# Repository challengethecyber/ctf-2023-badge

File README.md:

# ctf-2023-badge
Badge related files for CTC 2023 CTF

## Info

- Custom PCB with RP2040 based on [rp-micro](https://github.com/siderakb/rp-micro) project.
- View [IBOM](https://challengethecyber.github.io/ctf-2023-assets/ducky/ibom.html)

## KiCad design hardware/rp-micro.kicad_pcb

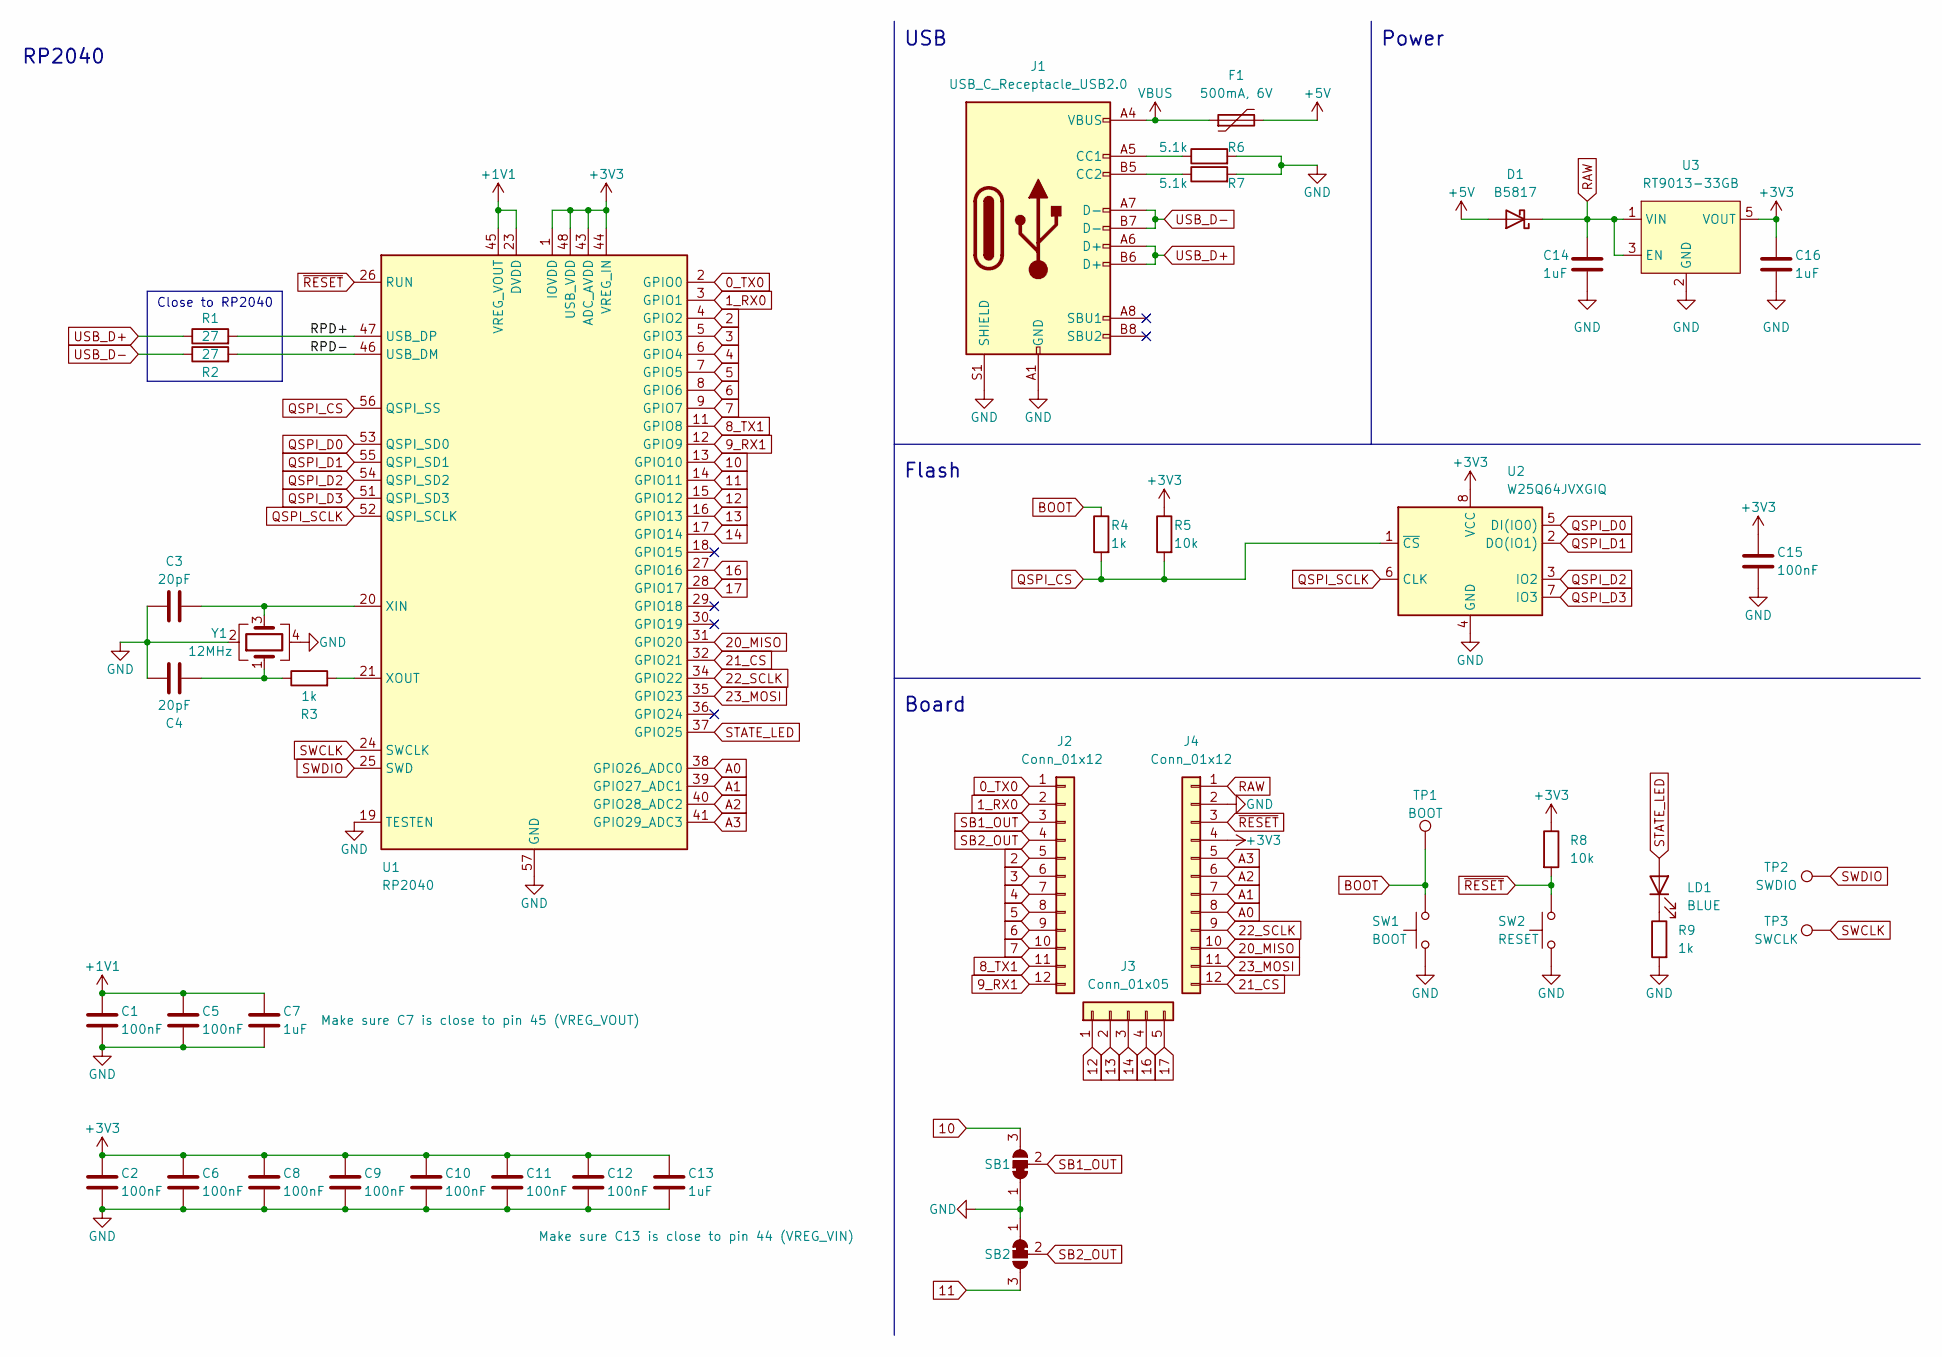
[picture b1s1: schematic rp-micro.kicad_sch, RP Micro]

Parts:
C1, C2, C5, C6, C8, C9, C10, C11, C12, C15: 100nF; C_0402_1005Metric; MFR. Part # CL05B104KB54PNC; JLCPCB Part # C307331
C3, C4: 20pF; C_0402_1005Metric; MFR. Part # 0402CG200J500NT; JLCPCB Part # C1554
C7, C13, C14, C16: 1uF; C_0402_1005Metric; MFR. Part # CL05A105KA5NQNC; JLCPCB Part # C52923
D1: B5817; D_SOD-323_HandSoldering; MFR. Part # B5817WS; JLCPCB Part # C123899
F1: 500mA, 6V; Fuse_0805_2012Metric; MFR. Part # SMD0805B050TF; JLCPCB Part # C269104
J1: USB_C_Receptacle_USB2.0; USB Type-C Mid-Mount Receptacle 16P; MFR. Part # 918-418K2024S40000; JLCPCB Part # C168688
J2, J4: Conn_01x12; PinHeader_1x12_P2.54mm_Vertical
J3: Conn_01x05; PinHeader_1x05_P2.54mm_Vertical
LD1: BLUE; LED_0603_1608Metric; MFR. Part # 19-217/BHC-ZL1M2RY/3T; JLCPCB Part # C72041
R1, R2: 27; R_0402_1005Metric; MFR. Part # 0402WGF270JTCE; JLCPCB Part # C25100
R3, R4, R9: 1k; R_0402_1005Metric; MFR. Part # 0402WGF1001TCE; JLCPCB Part # C11702
R5, R8: 10k; R_0402_1005Metric; MFR. Part # 0402WGF1002TCE; JLCPCB Part # C25744
R6, R7: 5.1k; R_0402_1005Metric; MFR. Part # 0402WGF5101TCE; JLCPCB Part # C25905
SB1, SB2: SolderJumper_3_Bridged12; SolderJumper-3_P1.3mm_Bridged12_Pad1.0x1.5mm
SW1: BOOT; SW_SPST_B3U-1000P; MFR. Part # B3U-1000P; JLCPCB Part # C231329
SW2: RESET; SW_SPST_B3U-1000P; MFR. Part # B3U-1000P; JLCPCB Part # C231329
TP1: BOOT; TestPoint_Pad_D2.0mm
TP2: SWDIO; TestPoint_Pad_D2.0mm
TP3: SWCLK; TestPoint_Pad_D2.0mm
U1: RP2040; QFN-56-1EP_7x7mm_P0.4mm_EP3.2x3.2mm; MFR. Part # RP2040; JLCPCB Part # C2040
U2: W25Q64JVXGIQ; XSON-8 (4x4mm); MFR. Part # W25Q64JVXGIQ; JLCPCB Part # C2940195
U3: RT9013-33GB; SOT-23-5; MFR. Part # RT9013-33GB; JLCPCB Part # C47773
Y1: 12MHz; Crystal_SMD_3225-4Pin_3.2x2.5mm; MFR. Part # X322512MSB4SI; JLCPCB Part # C9002

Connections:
0_TX0: J2.1, U1.2 (GPIO0)
1_RX0: J2.2, U1.3 (GPIO1)
2: J2.5, U1.4 (GPIO2)
3: J2.6, U1.5 (GPIO3)
4: J2.7, U1.6 (GPIO4)
5: J2.8, U1.7 (GPIO5)
6: J2.9, U1.8 (GPIO6)
7: J2.10, U1.9 (GPIO7)
8_TX1: J2.11, U1.11 (GPIO8)
9_RX1: J2.12, U1.12 (GPIO9)
10: SB1.3 (B), U1.13 (GPIO10)
11: SB2.3 (B), U1.14 (GPIO11)
12: J3.1, U1.15 (GPIO12)
13: J3.2, U1.16 (GPIO13)
14: J3.3, U1.17 (GPIO14)
16: J3.4, U1.27 (GPIO16)
17: J3.5, U1.28 (GPIO17)
20_MISO: J4.10, U1.31 (GPIO20)
21_CS: J4.12, U1.32 (GPIO21)
22_SCLK: J4.9, U1.34 (GPIO22)
23_MOSI: J4.11, U1.35 (GPIO23)
+1V1: C1.1, C5.1, C7.1, U1.23 (DVDD), U1.45 (VREG_VOUT), U1.50 (DVDD)
+3V3: C2.1, C6.1, C8.1, C9.1, C10.1, C11.1, C12.1, C13.1, C15.1, C16.1, J4.4, R5.1, R8.1, U1.1 (IOVDD), U1.10 (IOVDD), U1.22 (IOVDD), U1.33 (IOVDD), U1.42 (IOVDD), U1.43 (ADC_AVDD), U1.44 (VREG_IN), U1.48 (USB_VDD), U1.49 (IOVDD), U2.8 (VCC), U3.5 (VOUT)
+5V: D1.2 (A), F1.2
/RPD+: R1.2, U1.47 (USB_DP)
/RPD-: R2.2, U1.46 (USB_DM)
A0: J4.8, U1.38 (GPIO26_ADC0)
A1: J4.7, U1.39 (GPIO27_ADC1)
A2: J4.6, U1.40 (GPIO28_ADC2)
A3: J4.5, U1.41 (GPIO29_ADC3)
BOOT: R4.1, SW1.2, TP1.1
GND: C1.2, C2.2, C3.1, C4.1, C5.2, C6.2, C7.2, C8.2, C9.2, C10.2, C11.2, C12.2, C13.2, C14.2, C15.2, C16.2, J1.A1 (GND), J1.A12 (GND), J1.B1 (GND), J1.B12 (GND), J1.S1 (SHIELD), J4.2, R6.2, R7.2, R9.2, SB1.1 (A), SB2.1 (A), SW1.1, SW2.1, U1.19 (TESTEN), U1.57 (GND), U2.4 (GND), U3.2 (GND), Y1.2, Y1.4
unnamed: C3.2, U1.20 (XIN), Y1.3
unnamed: C4.2, R3.1, Y1.1
unnamed: J1.A5 (CC1), R6.1
unnamed: J1.B5 (CC2), R7.1
unnamed: LD1.1 (K), R9.1
unnamed: R3.2, U1.21 (XOUT)
QSPI_CS: R4.2, R5.2, U1.56 (QSPI_SS), U2.1 (~CS)
QSPI_D0: U1.53 (QSPI_SD0), U2.5 (DI(IO0))
QSPI_D1: U1.55 (QSPI_SD1), U2.2 (DO(IO1))
QSPI_D2: U1.54 (QSPI_SD2), U2.3 (IO2)
QSPI_D3: U1.51 (QSPI_SD3), U2.7 (IO3)
QSPI_SCLK: U1.52 (QSPI_SCLK), U2.6 (CLK)
RAW: C14.1, D1.1 (K), J4.1, U3.1 (VIN), U3.3 (EN)
SB1_OUT: J2.3, SB1.2 (C)
SB2_OUT: J2.4, SB2.2 (C)
STATE_LED: LD1.2 (A), U1.37 (GPIO25)
SWCLK: TP3.1, U1.24 (SWCLK)
SWDIO: TP2.1, U1.25 (SWD)
USB_D+: J1.A6 (D+), J1.B6 (D+), R1.1
USB_D-: J1.A7 (D-), J1.B7 (D-), R2.1
VBUS: F1.1, J1.A4 (VBUS), J1.A9 (VBUS), J1.B4 (VBUS), J1.B9 (VBUS)
~RESET: J4.3, R8.2, SW2.2, U1.26 (RUN)

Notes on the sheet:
Flash
Close to RP2040
Power
RP2040
USB
Board

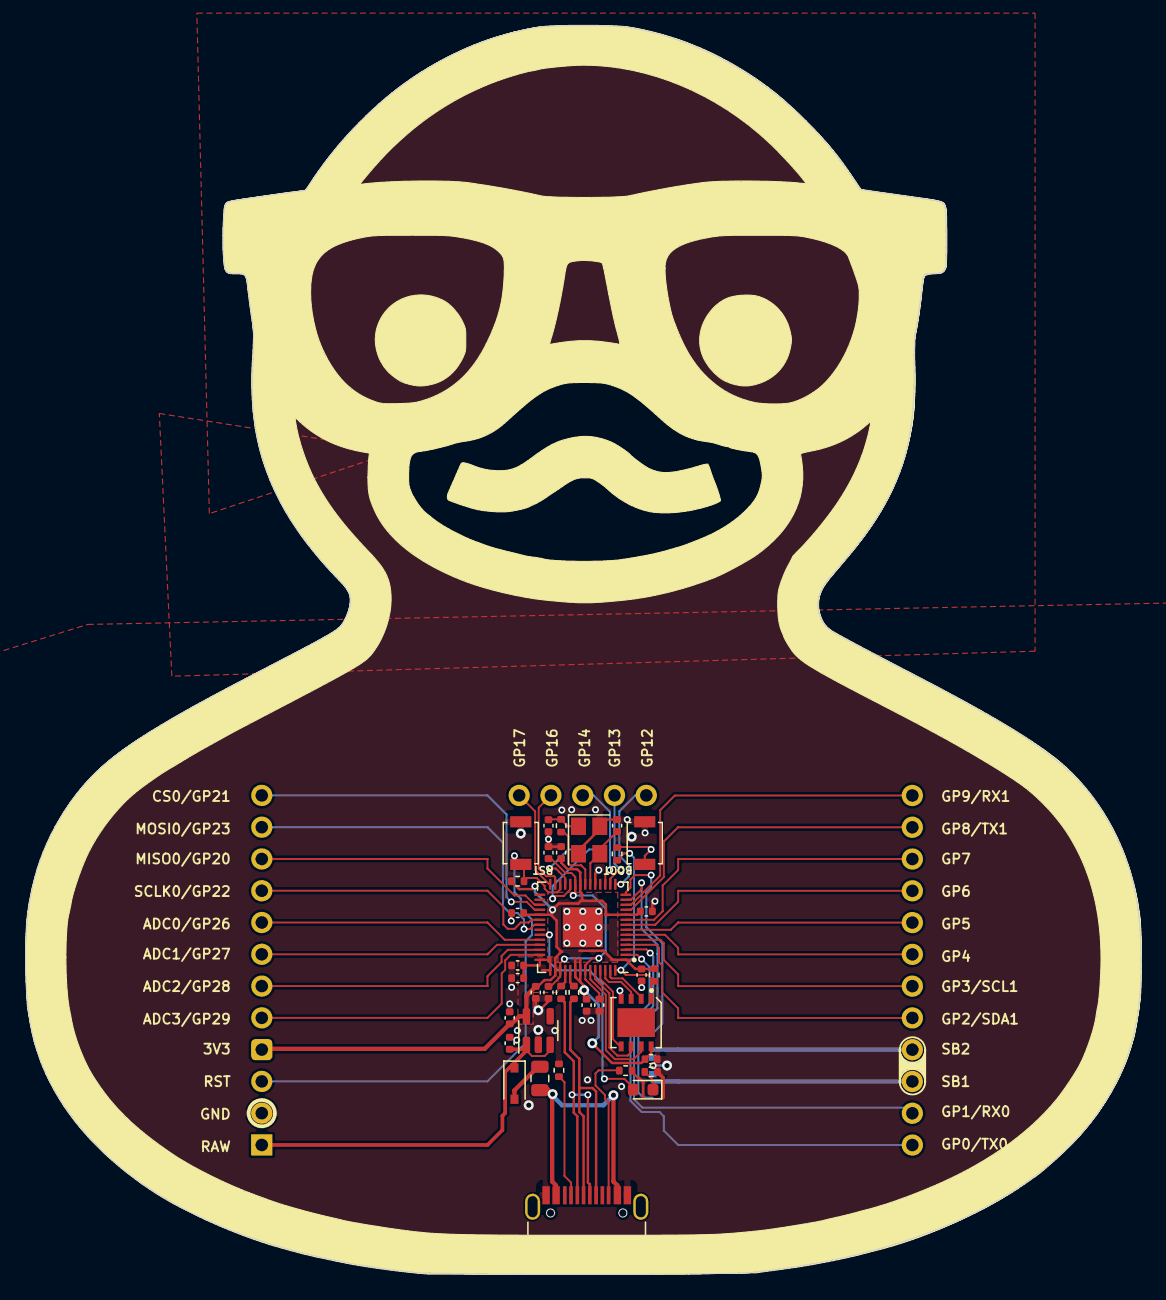
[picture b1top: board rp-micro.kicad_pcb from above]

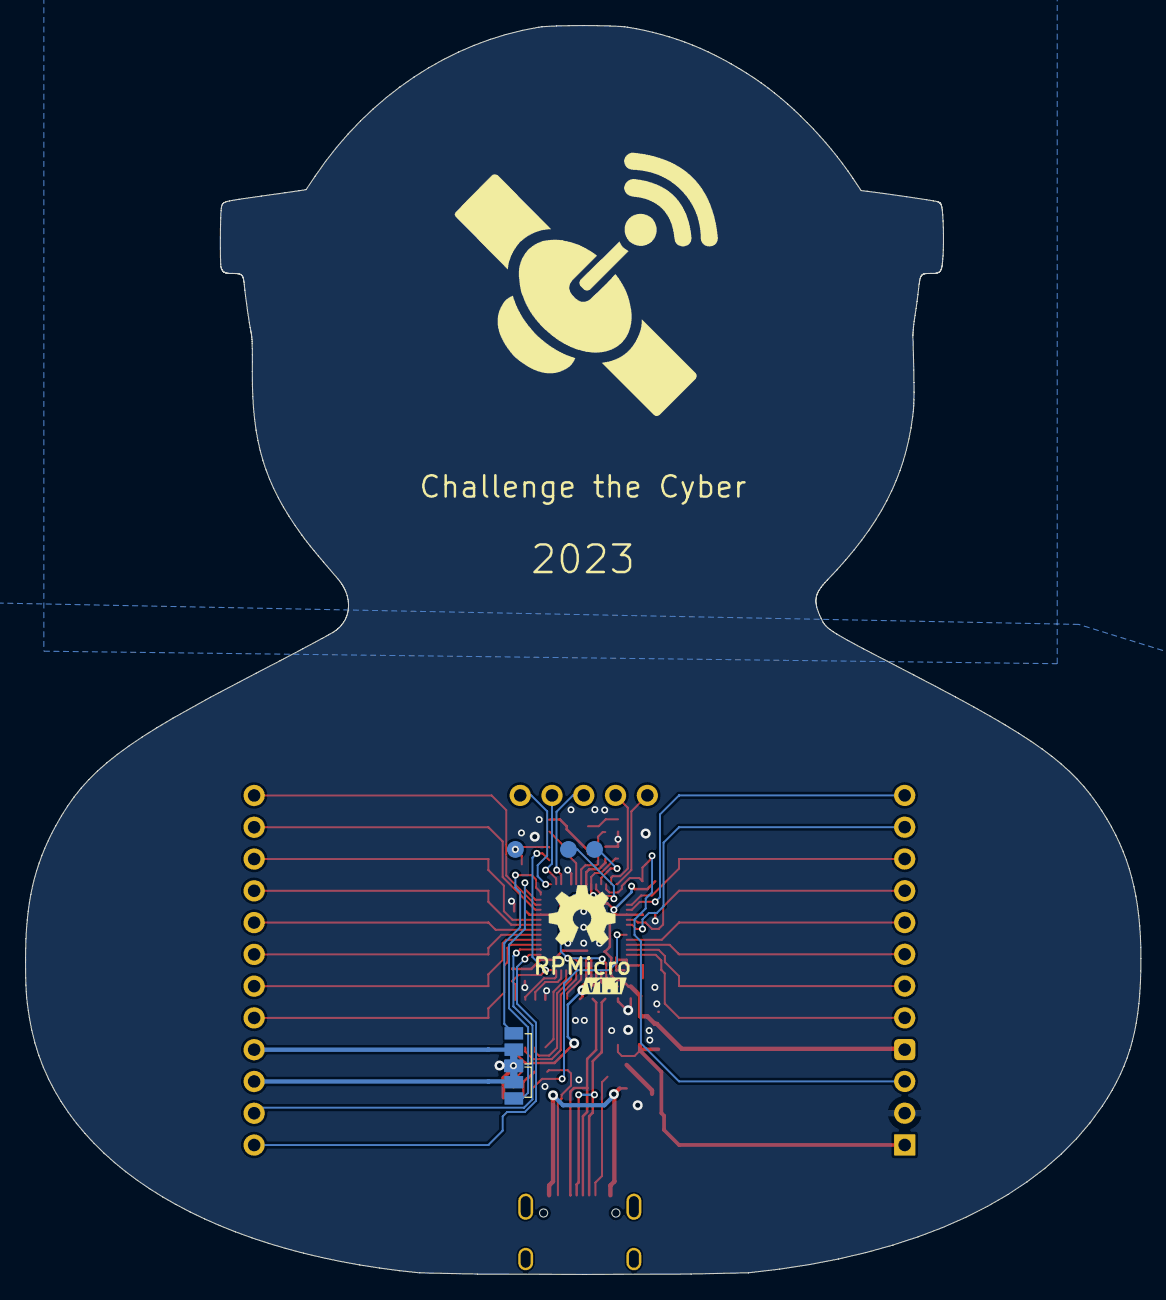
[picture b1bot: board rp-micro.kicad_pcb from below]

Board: 2 copper layers, 89.2 x 99.8 mm, 44 parts (8 on the bottom side), 54 nets.

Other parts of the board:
kibuzzard-637CA201: G***; kibuzzard-637CA201

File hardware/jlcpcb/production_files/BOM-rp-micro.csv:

Comment,Designator,Footprint,LCSC
1k,"R3,R4,R9",R_0402_1005Metric,C11702
B5817,D1,D_SOD-323_HandSoldering,C123899
20pF,"C3,C4",C_0402_1005Metric,C1554
RP2040,U1,QFN-56-1EP_7x7mm_P0.4mm_EP3.2x3.2mm,C2040
BOOT,"SW1,SW2",SW_SPST_B3U-1000P,C231329
27,"R1,R2",R_0402_1005Metric,C25100
10k,"R5,R8",R_0402_1005Metric,C25744
5.1k,"R6,R7",R_0402_1005Metric,C25905
"500mA, 6V",F1,Fuse_0805_2012Metric,C269104
W25Q64JVXGIQ,U2,XSON-8 (4x4mm),C2940195
100nF,"C1,C10,C11,C12,C15,C2,C5,C6,C8,C9",C_0402_1005Metric,C307331
RT9013-33GB,U3,SOT-23-5,C47773
1uF,"C13,C14,C16,C7",C_0402_1005Metric,C52923
BLUE,LD1,LED_0603_1608Metric,C72041
12MHz,Y1,Crystal_SMD_3225-4Pin_3.2x2.5mm,C9002
USB_C_Receptacle_USB2.0,J1,USB_C_Receptacle_TYPE-C-31-M-12,

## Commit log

2024-05-10 add files

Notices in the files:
hardware/rp-micro.kicad_pcb:
RP Micro has an MIT License (Open source hardware)
